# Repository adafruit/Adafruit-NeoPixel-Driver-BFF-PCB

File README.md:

## Adafruit NeoPixel Driver BFF PCB

<a href="http://www.adafruit.com/products/5645"><br/>
Click here to purchase one from the Adafruit shop</a>

PCB files for the Adafruit NeoPixel Driver BFF. 

Format is EagleCAD schematic and board layout
* https://www.adafruit.com/product/5645

### Description

Our QT Py boards are a great way to make very small microcontroller projects that pack a ton of power - and now we have a way for you to quickly add a strand of NeoPixels with a 5V level shifter and a detachable JST PH connector. It's an excellent way to make tiny wearable, cosplay or IoT projects with dazzling LEDs.

We call this the Adafruit NeoPixel Driver BFF - a "Best Friend Forever". When you were a kid you may have learned about the "buddy" system, well this product is kinda like that! A board that will watch your QT Py's back and give it the power and support to drive NeoPixel strips, rings, and panels.

This PCB is designed to fit onto the back of any QT Py or Xiao board, it can be soldered into place or use pin and socket headers to make it removable. Onboard is a 74AHCT125 single-gate level shifter that will take pin A3's output, and shift it up to 5V using the USB power as a reference. The USB power, ground and shifted data is then piped out to a JST PH 2mm 3-pin connector.

If using one of our NeoPixel strips with a JST-PH connector on them already, you can just plug it right in for instant lights. If you're using a common JST SH (black in-line) connector on the strips, you can use a JST-PH-to-female-header cable and use that to plug into the pins on the input of the SH port and/or can jam the wires into the header sockets. 

Note that we connect the USB 5V power directly out to the NeoPixel power pin on the JST PH connector and PH connectors are only rated for about 2 Amps, so it's not for powering directly more than maybe 30-60 NeoPixels (less if they're on full white brightness). 

We include some header that you can solder to your QT Py. You can also pick up an Itsy Bitsy short female header kit to make it removable but compact, you'll just need to trim down the headers to 7 pins long.

Comes as an assembled and tested PCB
For any QT Py or Xiao boards
Uses the 5V input via USB Type-C connector on QT Py to Power 30ish NeoPixels
Level-shifted data from pin A3 default, can solder-jumper select SCL, TX, RX, SCK or MOSI
For driving any WS2812/WS2811/NeoPixel LEDs
NeoPixels and QT Py are not included.

### License

Adafruit invests time and resources providing this open source design, please support Adafruit and open-source hardware by purchasing products from [Adafruit](https://www.adafruit.com)!

Designed by Limor Fried/Ladyada for Adafruit Industries.

Creative Commons Attribution/Share-Alike, all text above must be included in any redistribution. 
See license.txt for additional details.

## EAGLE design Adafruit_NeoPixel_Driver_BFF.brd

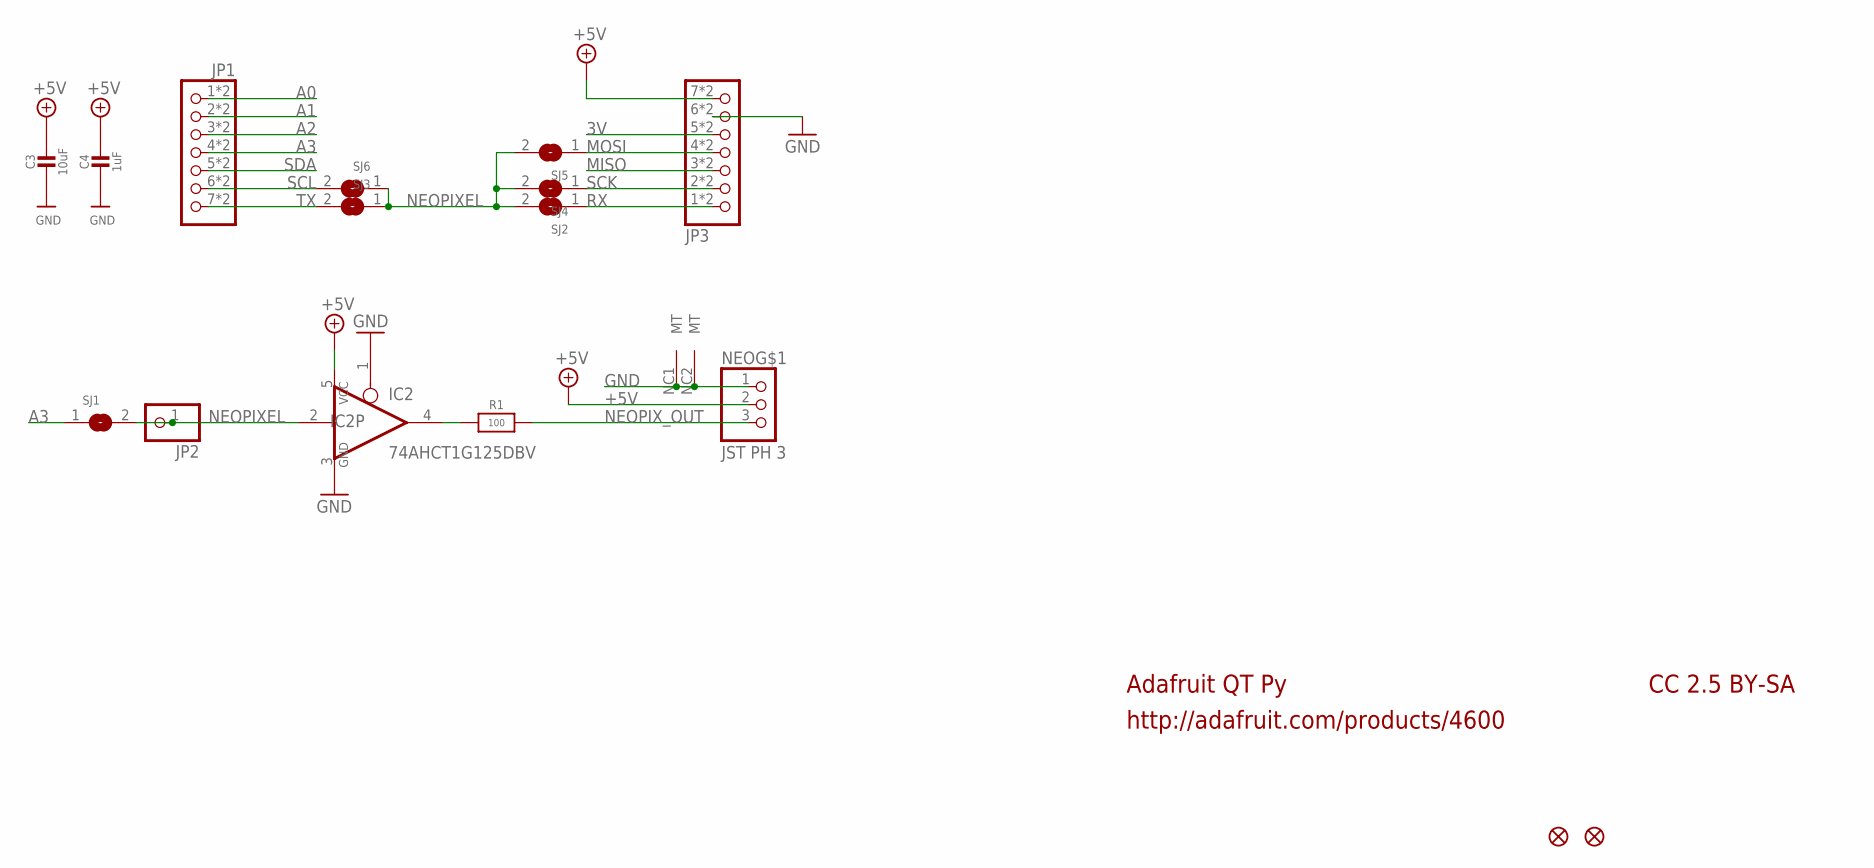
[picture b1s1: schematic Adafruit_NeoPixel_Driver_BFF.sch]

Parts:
C3: 10uF; 0805-NO
C4: 1uF; 0603-NO
IC2: 74AHCT1G125DBV; SOT23-5
JP1, JP3: HEADER-1X7_CASTEL; 1X07_CASTEL
JP2: HEADER-1X1ROUND_76MIL; 1X01_ROUND_76MIL
NEO: JST PH 3; JSTPH3
R1: 100; 0603-NO
SJ1: SOLDERJUMPERCLOSED; SOLDERJUMPER_CLOSEDWIRE
SJ2, SJ3, SJ4, SJ5, SJ6: SOLDERJUMPER; SOLDERJUMPER_ARROW_NOPASTE
U$6, U$8: FIDUCIAL_1MM

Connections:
3V: JP3.5, JP3.5C (5)
+5V: C3.1, C4.1, IC2.5 (VCC), JP3.7, JP3.7C (7), NEO.2
A0: JP1.1, JP1.1C (1)
A1: JP1.2, JP1.2C (2)
A2: JP1.3, JP1.3C (3)
A3: JP1.4, JP1.4C (4), SJ1.1
GND: C3.2, C4.2, IC2.1 (OE), IC2.3 (GND), JP3.6, JP3.6C (6), NEO.1, NEO.NC1 (MT), NEO.NC2 (MT)
MISO: JP3.3, JP3.3C (3)
MOSI: JP3.4, JP3.4C (4), SJ5.1
unnamed: IC2.4 (O), R1.1
NEOPIXEL: IC2.2 (I), JP2.1, SJ1.2, SJ2.2, SJ3.1, SJ4.2, SJ5.2, SJ6.1
NEOPIX_OUT: NEO.3, R1.2
RX: JP3.1, JP3.1C (1), SJ2.1
SCK: JP3.2, JP3.2C (2), SJ4.1
SCL: JP1.6, JP1.6C (6), SJ6.2
SDA: JP1.5, JP1.5C (5)
TX: JP1.7, JP1.7C (7), SJ3.2

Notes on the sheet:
Adafruit QT Py
http://adafruit.com/products/4600
CC 2.5 BY-SA

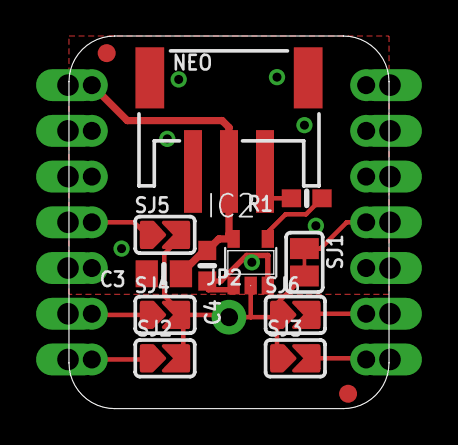
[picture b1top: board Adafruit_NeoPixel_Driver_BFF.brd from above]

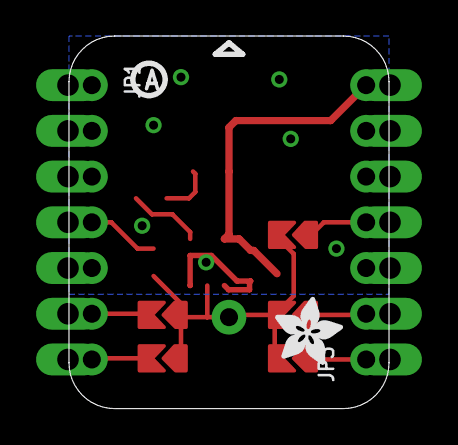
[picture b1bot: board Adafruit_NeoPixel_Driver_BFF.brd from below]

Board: 2 copper layers, 17.8 x 20.7 mm, 39 parts (6 on the bottom side), 17 nets.

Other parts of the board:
PLABEL0: PLABEL0
PLABEL1: PLABEL1
PLABEL2: PLABEL2
PLABEL3: PLABEL3
PLABEL4: PLABEL4
PLABEL5: PLABEL5
PLABEL6: PLABEL6
PLABEL7: PLABEL7
PLABEL8: PLABEL8
PLABEL9: PLABEL9
PLABEL10: PLABEL10
PLABEL11: PLABEL11
PLABEL12: PLABEL12
PLABEL13: PLABEL13
PLABEL14: PLABEL14
PLABEL15: PLABEL15
PLABEL16: PLABEL16
PLABEL17: PLABEL17
PLABEL18: PLABEL18
PLABEL19: PLABEL19
PLABEL20: PLABEL20
U$2: ADAFRUIT_3.5MM
U$3: PCBFEAT-REV-040

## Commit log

2022-11-22 Adding cookiecutter output

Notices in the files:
parts and their libraries:
microbuilder: This work is placed in the public domain, and may be freely used for commercial and non-commercial work with the following conditions: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
